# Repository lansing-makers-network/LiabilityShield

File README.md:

An Arduino shield inspired by SparkFun's Danger Shield.

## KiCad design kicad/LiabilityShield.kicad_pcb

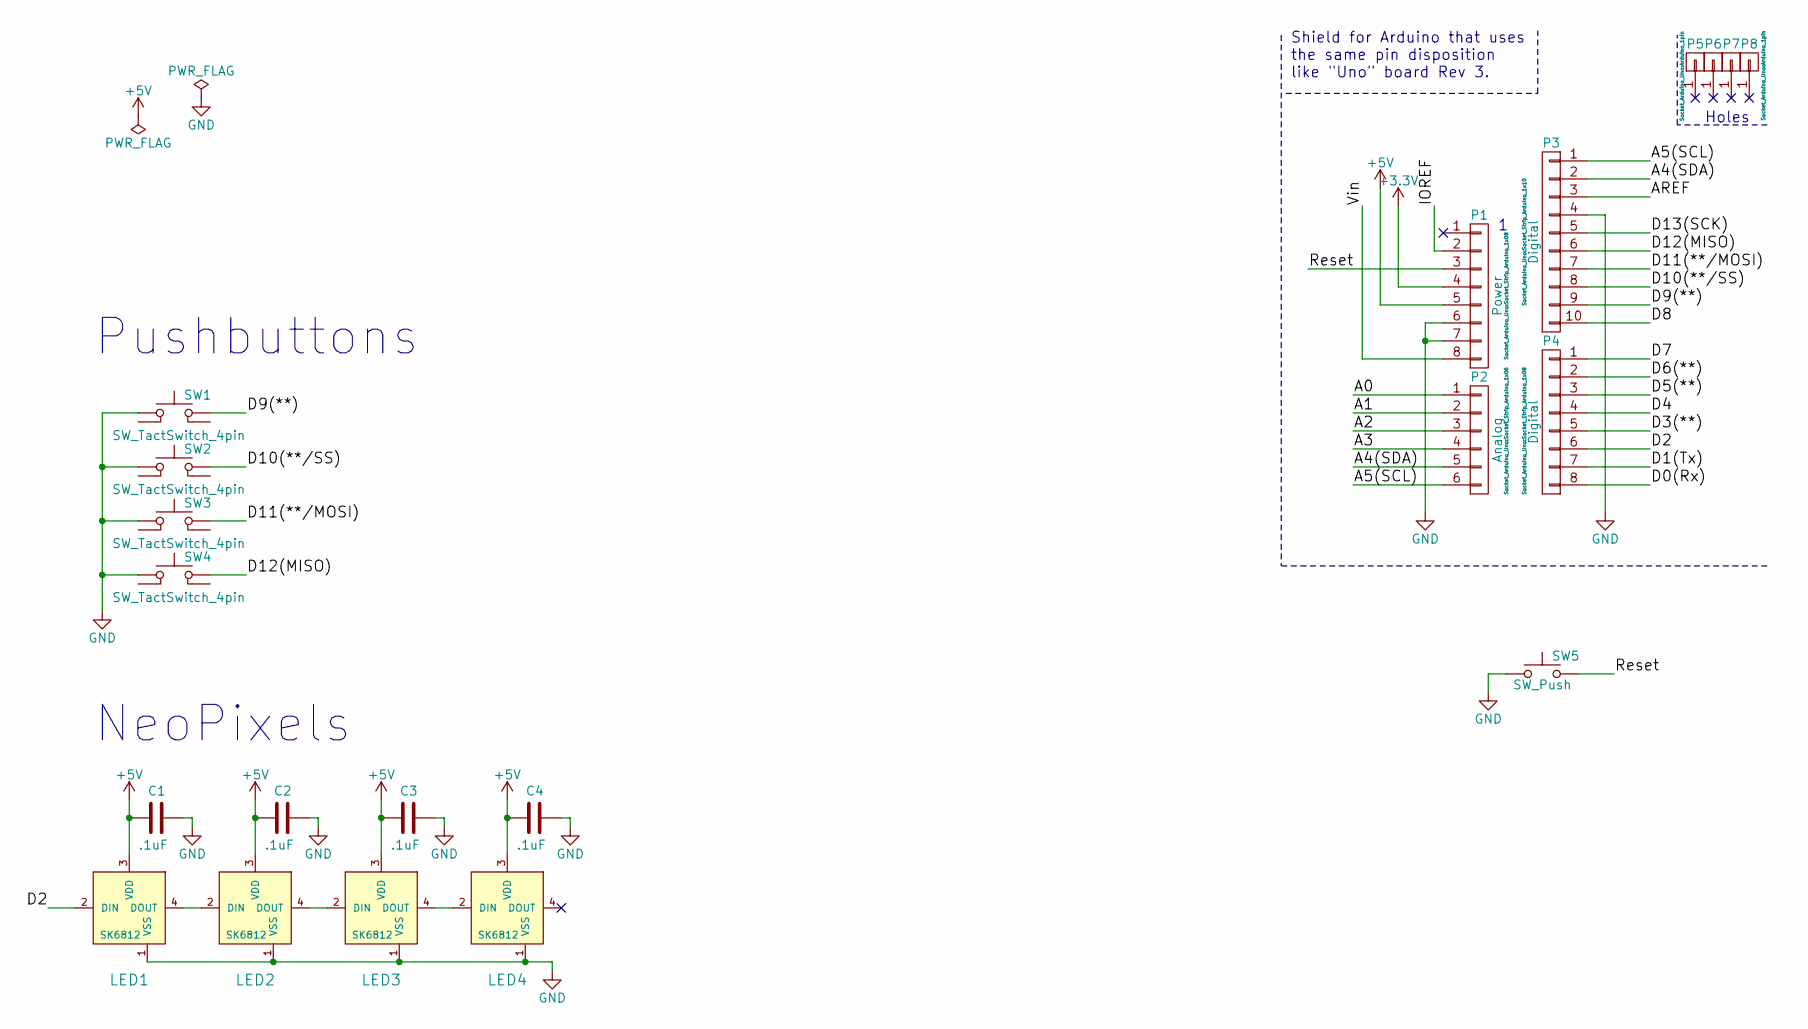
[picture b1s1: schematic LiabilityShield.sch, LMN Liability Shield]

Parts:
C1, C2, C3, C4: .1uF; C_0805_HandSoldering
LED1, LED2, LED3, LED4: SK6812; LED_5050_4pin
P1: Power; Socket_Strip_Arduino_1x08
P2: Analog; Socket_Strip_Arduino_1x06
P3: Digital; Socket_Strip_Arduino_1x10
P4: Digital; Socket_Strip_Arduino_1x08
P5, P6, P7, P8: CONN_01X01; Arduino_1pin
SW1, SW2, SW3, SW4: SW_TactSwitch_4pin; TactSwitch_12.5_5
SW5: SW_Push; TactSwitch_6.5_4.5

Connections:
+3V3: P1.4
+5V: C1.2, C2.2, C3.2, C4.2, LED1.3 (VDD), LED2.3 (VDD), LED3.3 (VDD), LED4.3 (VDD), P1.5
/A0: P2.1
/A1: P2.2
/A2: P2.3
/A3: P2.4
/A4(SDA): P2.5, P3.2
/A5(SCL): P2.6, P3.1
/AREF: P3.3
/D0(Rx): P4.8
/D1(Tx): P4.7
/D2: LED1.2 (DIN), P4.6
/D3(**): P4.5
/D4: P4.4
/D5(**): P4.3
/D6(**): P4.2
/D7: P4.1
/D8: P3.10
/D9(**): P3.9, SW1.3 (B)
/D10(**/SS): P3.8, SW2.3 (B)
/D11(**/MOSI): P3.7, SW3.3 (B)
/D12(MISO): P3.6, SW4.3 (B)
/D13(SCK): P3.5
/IOREF: P1.2
/Reset: P1.3, SW5.2
/Vin: P1.8
GND: C1.1, C2.1, C3.1, C4.1, LED1.1 (VSS), LED2.1 (VSS), LED3.1 (VSS), LED4.1 (VSS), P1.6, P1.7, P3.4, SW1.1 (A), SW2.1 (A), SW3.1 (A), SW4.1 (A), SW5.1
unnamed: LED1.4 (DOUT), LED2.2 (DIN)
unnamed: LED2.4 (DOUT), LED3.2 (DIN)
unnamed: LED3.4 (DOUT), LED4.2 (DIN)

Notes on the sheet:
Holes
Shield for Arduino that uses the same pin disposition like "Uno" board Rev 3.
NeoPixels
Pushbuttons

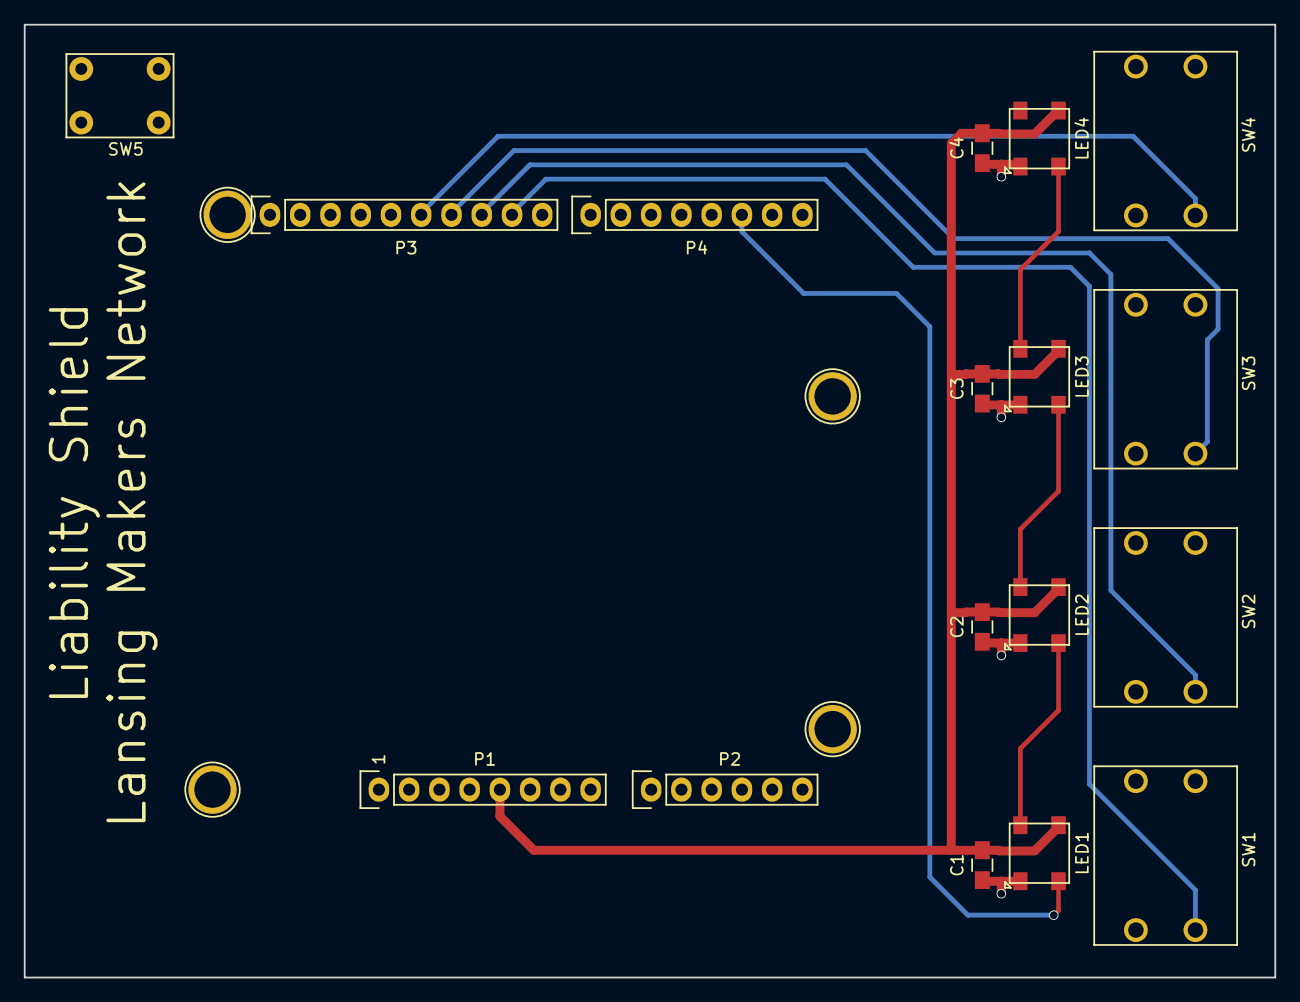
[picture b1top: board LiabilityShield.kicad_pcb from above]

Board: 2 copper layers, 105.0 x 80.0 mm, 21 parts (0 on the bottom side), 13 nets.

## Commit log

2018-01-02 Board defined
    Minimal schematic and board layout
2018-01-02 Add images to README.md
